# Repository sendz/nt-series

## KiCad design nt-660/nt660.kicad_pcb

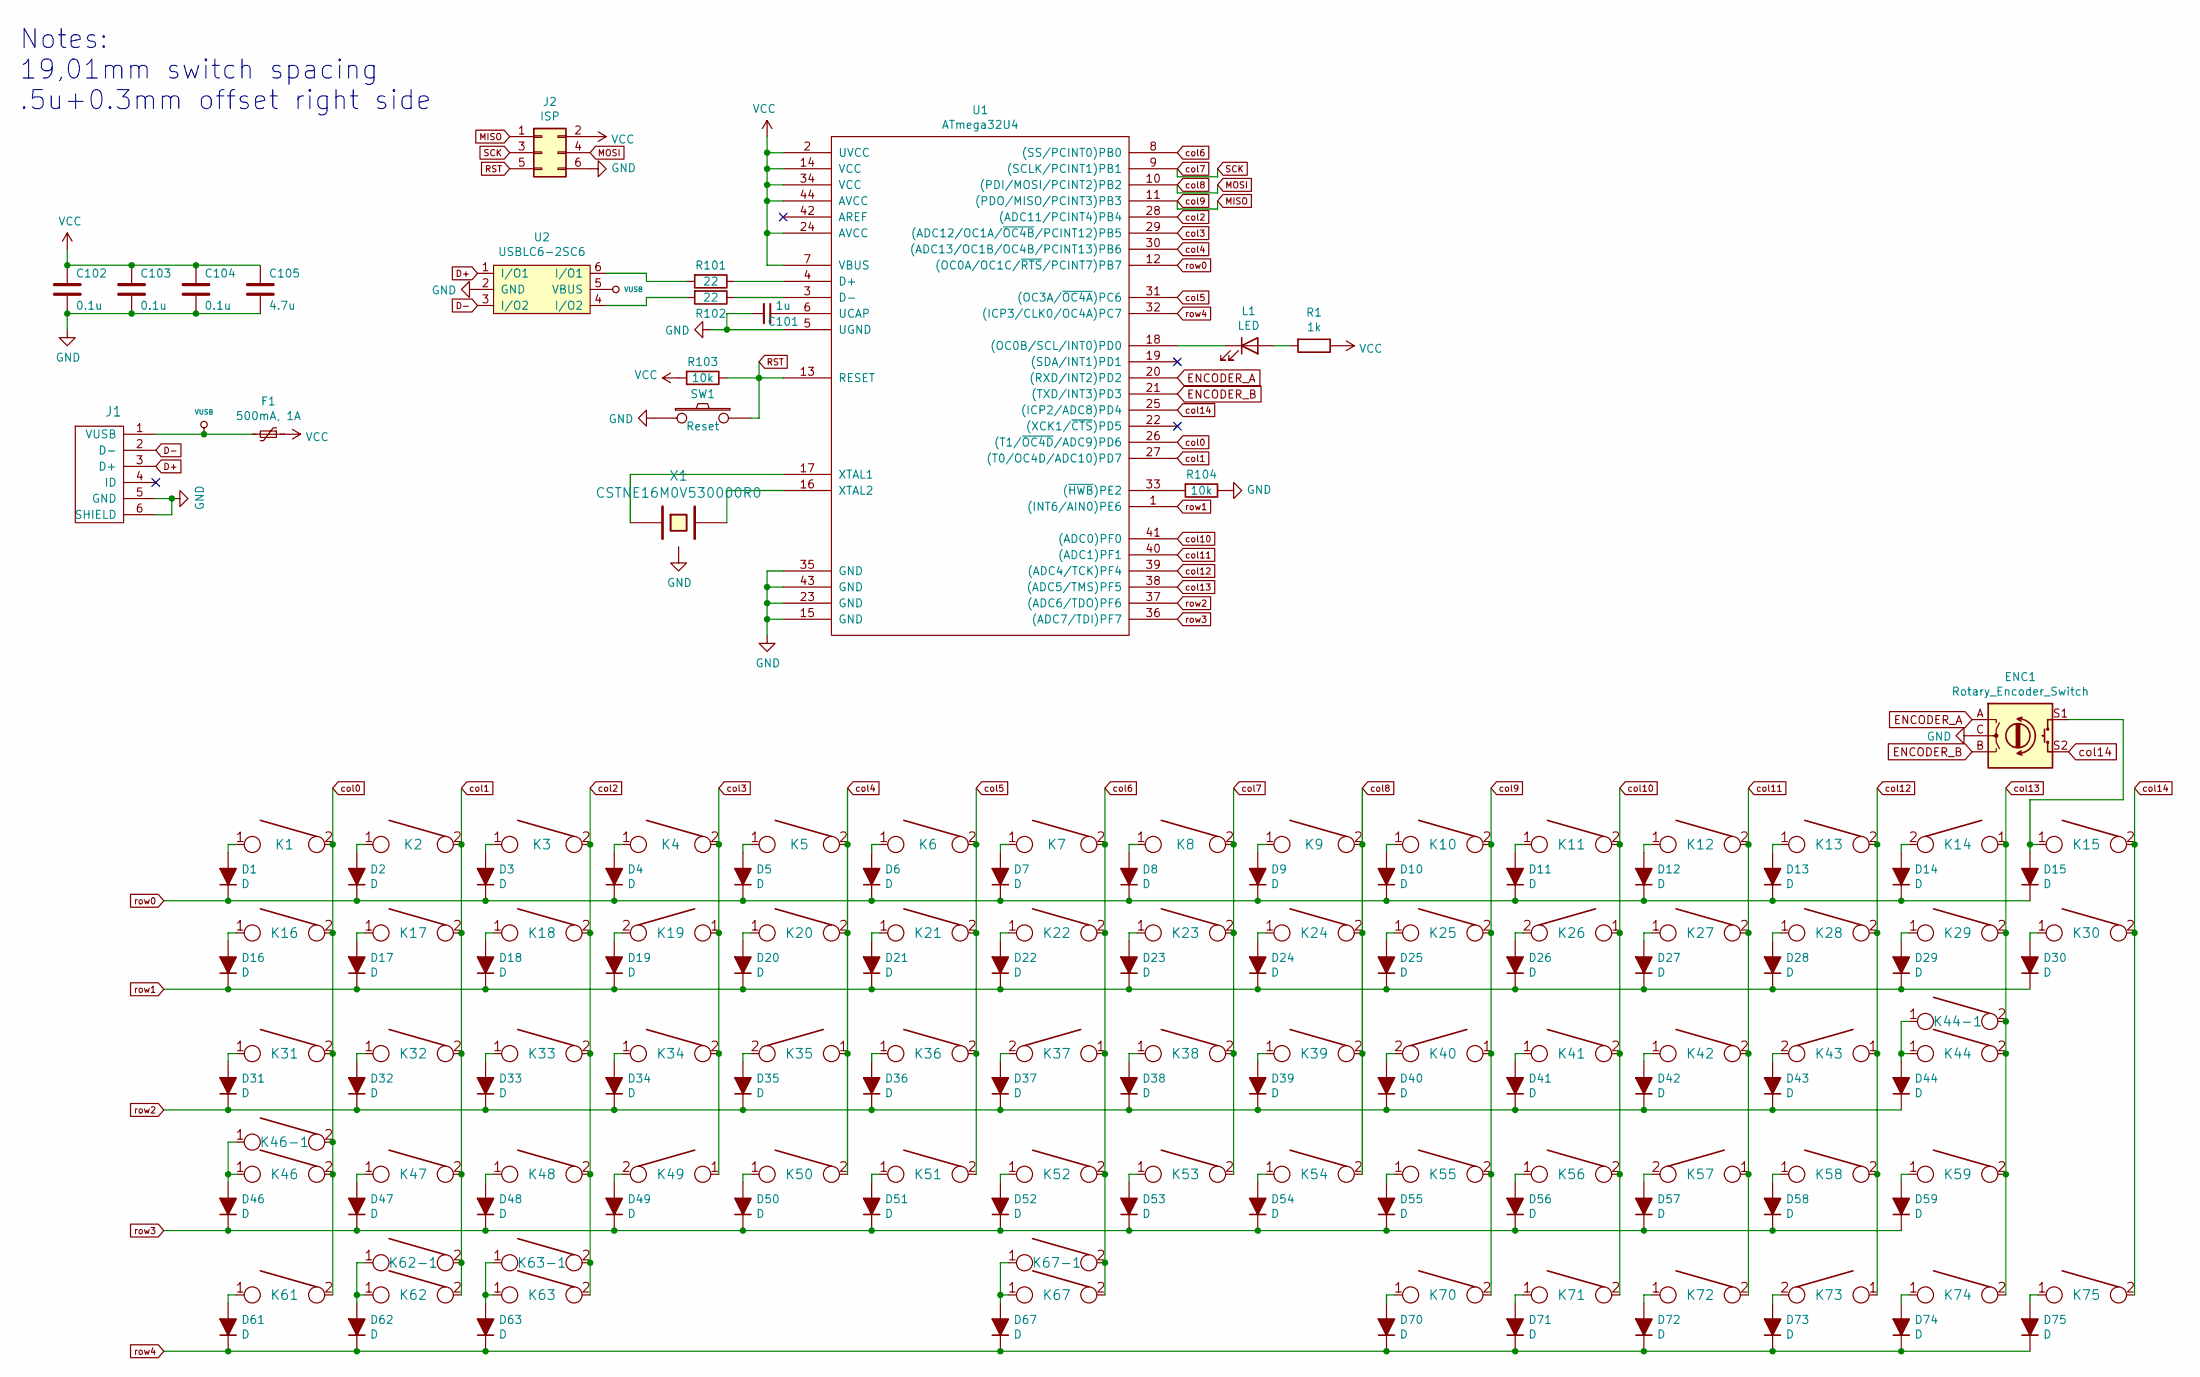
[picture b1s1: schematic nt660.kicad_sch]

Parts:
C101: 1u; C_0805
C102, C103, C104: 0.1u; C_0805
C105: 4.7u; C_0805
D1, D2, D3, D4, D5, D6, D7, D8, D9, D10, D11, D12, D13, D14, D15, D16, D17, D18, D19, D20, D21, D22, D23, D24, D25, D26, D27, D28, D29, D30, D31, D32, D33, D34, D35, D36, D37, D38, D39, D40, D41, D42, D43, D44, D46, D47, D48, D49, D50, D51, D52, D53, D54, D55, D56, D57, D58, D59, D61, D62, D63, D67, D70, D71, D72, D73, D74, D75: D; D_SOD-123
ENC1: Rotary_Encoder_Switch; RotaryEncoder_Alps_EC11E-Switch_Vertical_H20mm
F1: 500mA, 1A; R_0805
J1: USB_mini_micro_B; USB-Mini-B_ LCSC-C46398
J2: ISP; isp_standard
K1, K2, K3, K4, K5, K6, K7, K8, K9, K10, K11, K12, K13, K15, K17, K18, K19, K20, K21, K22, K23, K24, K25, K26, K27, K28, K30, K32, K33, K34, K35, K36, K37, K38, K39, K40, K41, K42, K43, K47, K48, K49, K50, K51, K52, K53, K54, K55, K56, K57, K59, K62, K73, K74, K75: KEYSW; CHERRY_PLATE_100H
K14: KEYSW; CHERRY_PCB_200H
K16, K29: KEYSW; CHERRY_PLATE_150H
K31: KEYSW; CHERRY_PLATE_175H
K44, K46, K58: KEYSW; CHERRY_PCB_225H
K44-1: KEYSW; CHERRY_PCB_200H_V
K46-1, K61, K62-1, K63, K63-1, K70, K71, K72: KEYSW; CHERRY_PLATE_125H
K67: KEYSW; CHERRY_PCB_625H_F
K67-1: KEYSW; CHERRY_PCB_600C_H_F
L1: LED; CHERRY_MX_LED
R1: 1k; R_0805
R101, R102: 22; R_0805
R103, R104: 10k; R_0805
SW1: Reset; SW_SPST_TL3342
U1: ATmega32U4; ATMEGA32U4
U2: USBLC6-2SC6
X1: CSTNE16M0V530000R0; Resonator_SMD_muRata_CSTNExxV-3Pin-p1.2

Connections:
D+: J1.3 (D+), U2.1 (I/O1)
D-: J1.2 (D-), U2.3 (I/O2)
ENCODER_A: ENC1.A, U1.20 ((RXD/INT2)PD2)
ENCODER_B: ENC1.B, U1.21 ((TXD/INT3)PD3)
GND: C101.2, C102.2, C103.2, C104.2, C105.2, ENC1.C, J1.5 (GND), J1.6 (SHIELD), J2.6, R104.1, SW1.1, U1.5 (UGND), U1.15 (GND), U1.23 (GND), U1.35 (GND), U1.43 (GND), U2.2 (GND), X1.3
MISO: J2.1, K10.2, K25.2, K40.1, K55.2, K70.2, U1.11 ((PDO/MISO/PCINT3)PB3)
MOSI: J2.4, K9.2, K24.2, K39.2, K54.2, U1.10 ((PDI/MOSI/PCINT2)PB2)
unnamed: C101.1, U1.6 (UCAP)
unnamed: D1.2 (A), K1.1
unnamed: D2.2 (A), K2.1
unnamed: D3.2 (A), K3.1
unnamed: D4.2 (A), K4.1
unnamed: D5.2 (A), K5.1
unnamed: D6.2 (A), K6.1
unnamed: D7.2 (A), K7.1
unnamed: D8.2 (A), K8.1
unnamed: D9.2 (A), K9.1
unnamed: D10.2 (A), K10.1
unnamed: D11.2 (A), K11.1
unnamed: D12.2 (A), K12.1
unnamed: D13.2 (A), K13.1
unnamed: D14.2 (A), K14.2
unnamed: D15.2 (A), ENC1.S1, K15.1
unnamed: D16.2 (A), K16.1
unnamed: D17.2 (A), K17.1
unnamed: D18.2 (A), K18.1
unnamed: D19.2 (A), K19.2
unnamed: D20.2 (A), K20.1
unnamed: D21.2 (A), K21.1
unnamed: D22.2 (A), K22.1
unnamed: D23.2 (A), K23.1
unnamed: D24.2 (A), K24.1
unnamed: D25.2 (A), K25.1
unnamed: D26.2 (A), K26.2
unnamed: D27.2 (A), K27.1
unnamed: D28.2 (A), K28.1
unnamed: D29.2 (A), K29.1
unnamed: D30.2 (A), K30.1
unnamed: D31.2 (A), K31.1
unnamed: D32.2 (A), K32.1
unnamed: D33.2 (A), K33.1
unnamed: D34.2 (A), K34.1
unnamed: D35.2 (A), K35.2
unnamed: D36.2 (A), K36.1
unnamed: D37.2 (A), K37.2
unnamed: D38.2 (A), K38.1
unnamed: D39.2 (A), K39.1
unnamed: D40.2 (A), K40.2
unnamed: D41.2 (A), K41.1
unnamed: D42.2 (A), K42.1
unnamed: D43.2 (A), K43.2
unnamed: D44.2 (A), K44.1, K44-1.1
unnamed: D46.2 (A), K46.1, K46-1.1
unnamed: D47.2 (A), K47.1
unnamed: D48.2 (A), K48.1
unnamed: D49.2 (A), K49.2
unnamed: D50.2 (A), K50.1
unnamed: D51.2 (A), K51.1
unnamed: D52.2 (A), K52.1
unnamed: D53.2 (A), K53.1
unnamed: D54.2 (A), K54.1
unnamed: D55.2 (A), K55.1
unnamed: D56.2 (A), K56.1
unnamed: D57.2 (A), K57.2
unnamed: D58.2 (A), K58.1
unnamed: D59.2 (A), K59.1
unnamed: D61.2 (A), K61.1
unnamed: D62.2 (A), K62.1, K62-1.1
unnamed: D63.2 (A), K63.1, K63-1.1
unnamed: D67.2 (A), K67.1, K67-1.1
unnamed: D70.2 (A), K70.1
unnamed: D71.2 (A), K71.1
unnamed: D72.2 (A), K72.1
unnamed: D73.2 (A), K73.2
unnamed: D74.2 (A), K74.1
unnamed: D75.2 (A), K75.1
unnamed: L1.1 (K), U1.18 ((OC0B/SCL/INT0)PD0)
unnamed: L1.2 (A), R1.2
unnamed: R101.1, U1.4 (D+)
unnamed: R101.2, U2.6 (I/O1)
unnamed: R102.1, U1.3 (D-)
unnamed: R102.2, U2.4 (I/O2)
unnamed: R104.2, U1.33 ((~HWB~)PE2)
unnamed: U1.16 (XTAL2), X1.2
unnamed: U1.17 (XTAL1), X1.1
RST: J2.5, R103.1, SW1.2, U1.13 (RESET)
SCK: J2.3, K8.2, K23.2, K38.2, K53.2, U1.9 ((SCLK/PCINT1)PB1)
VCC: C102.1, C103.1, C104.1, C105.1, F1.1, J2.2, R1.1, R103.2, U1.2 (UVCC), U1.7 (VBUS), U1.14 (VCC), U1.24 (AVCC), U1.34 (VCC), U1.44 (AVCC)
VUSB: F1.2, J1.1 (VUSB), U2.5 (VBUS)
col0: K1.2, K16.2, K31.2, K46.2, K46-1.2, K61.2, U1.26 ((T1/~OC4D~/ADC9)PD6)
col1: K2.2, K17.2, K32.2, K47.2, K62.2, K62-1.2, U1.27 ((T0/OC4D/ADC10)PD7)
col2: K3.2, K18.2, K33.2, K48.2, K63.2, K63-1.2, U1.28 ((ADC11/PCINT4)PB4)
col3: K4.2, K19.1, K34.2, K49.1, U1.29 ((ADC12/OC1A/~OC4B~/PCINT12)PB5)
col4: K5.2, K20.2, K35.1, K50.2, U1.30 ((ADC13/OC1B/OC4B/PCINT13)PB6)
col5: K6.2, K21.2, K36.2, K51.2, U1.31 ((OC3A/~OC4A~)PC6)
col6: K7.2, K22.2, K37.1, K52.2, K67.2, K67-1.2, U1.8 ((SS/PCINT0)PB0)
col10: K11.2, K26.1, K41.2, K56.2, K71.2, U1.41 ((ADC0)PF0)
col11: K12.2, K27.2, K42.2, K57.1, K72.2, U1.40 ((ADC1)PF1)
col12: K13.2, K28.2, K43.1, K58.2, K73.1, U1.39 ((ADC4/TCK)PF4)
col13: K14.1, K29.2, K44.2, K44-1.2, K59.2, K74.2, U1.38 ((ADC5/TMS)PF5)
col14: ENC1.S2, K15.2, K30.2, K75.2, U1.25 ((ICP2/ADC8)PD4)
row0: D1.1 (K), D2.1 (K), D3.1 (K), D4.1 (K), D5.1 (K), D6.1 (K), D7.1 (K), D8.1 (K), D9.1 (K), D10.1 (K), D11.1 (K), D12.1 (K), D13.1 (K), D14.1 (K), D15.1 (K), U1.12 ((OC0A/OC1C/~RTS~/PCINT7)PB7)
row1: D16.1 (K), D17.1 (K), D18.1 (K), D19.1 (K), D20.1 (K), D21.1 (K), D22.1 (K), D23.1 (K), D24.1 (K), D25.1 (K), D26.1 (K), D27.1 (K), D28.1 (K), D29.1 (K), D30.1 (K), U1.1 ((INT6/AIN0)PE6)
row2: D31.1 (K), D32.1 (K), D33.1 (K), D34.1 (K), D35.1 (K), D36.1 (K), D37.1 (K), D38.1 (K), D39.1 (K), D40.1 (K), D41.1 (K), D42.1 (K), D43.1 (K), D44.1 (K), U1.37 ((ADC6/TDO)PF6)
row3: D46.1 (K), D47.1 (K), D48.1 (K), D49.1 (K), D50.1 (K), D51.1 (K), D52.1 (K), D53.1 (K), D54.1 (K), D55.1 (K), D56.1 (K), D57.1 (K), D58.1 (K), D59.1 (K), U1.36 ((ADC7/TDI)PF7)
row4: D61.1 (K), D62.1 (K), D63.1 (K), D67.1 (K), D70.1 (K), D71.1 (K), D72.1 (K), D73.1 (K), D74.1 (K), D75.1 (K), U1.32 ((ICP3/CLK0/OC4A)PC7)

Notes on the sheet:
Notes: 19,01mm switch spacing .5u+0.3mm offset right side

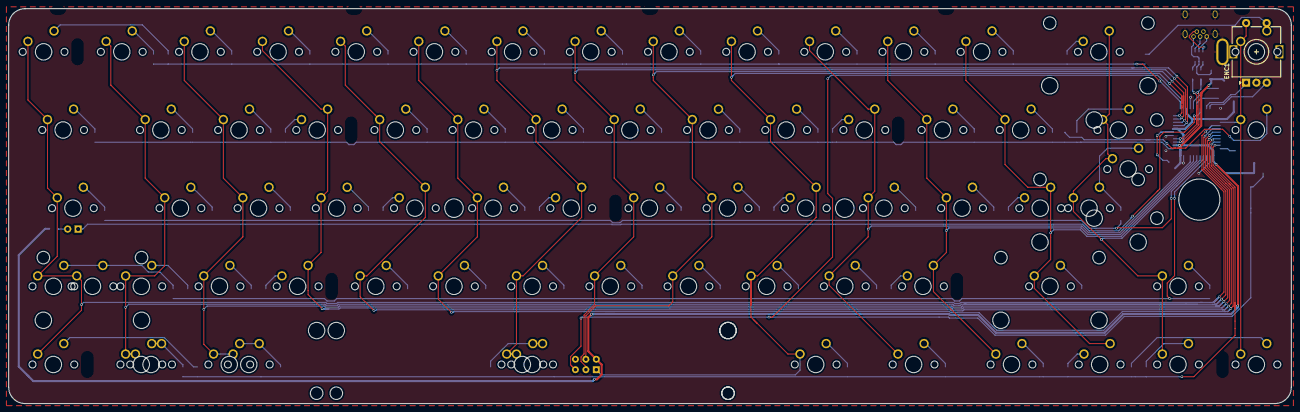
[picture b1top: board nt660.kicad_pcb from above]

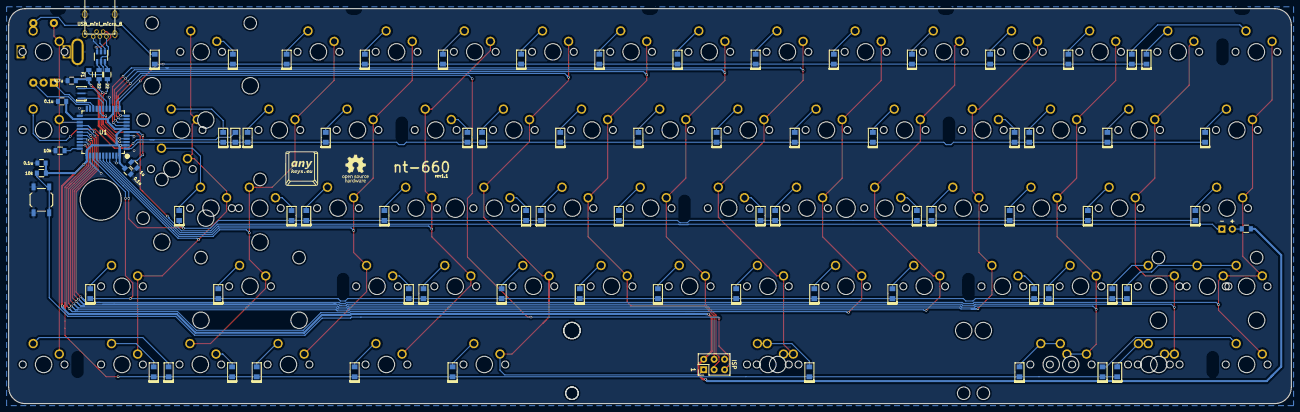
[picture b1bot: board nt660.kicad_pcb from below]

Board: 2 copper layers, 312.0 x 96.1 mm, 160 parts (85 on the bottom side), 106 nets.

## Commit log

2020-10-06 Upload PCB files
2020-10-06 Add readme's
2020-10-25 nt-660 rev1.1
2020-10-25 Add PCB images
2020-10-25 fix images
2020-12-01 Add rotary encoder and change USB footprint to THT
